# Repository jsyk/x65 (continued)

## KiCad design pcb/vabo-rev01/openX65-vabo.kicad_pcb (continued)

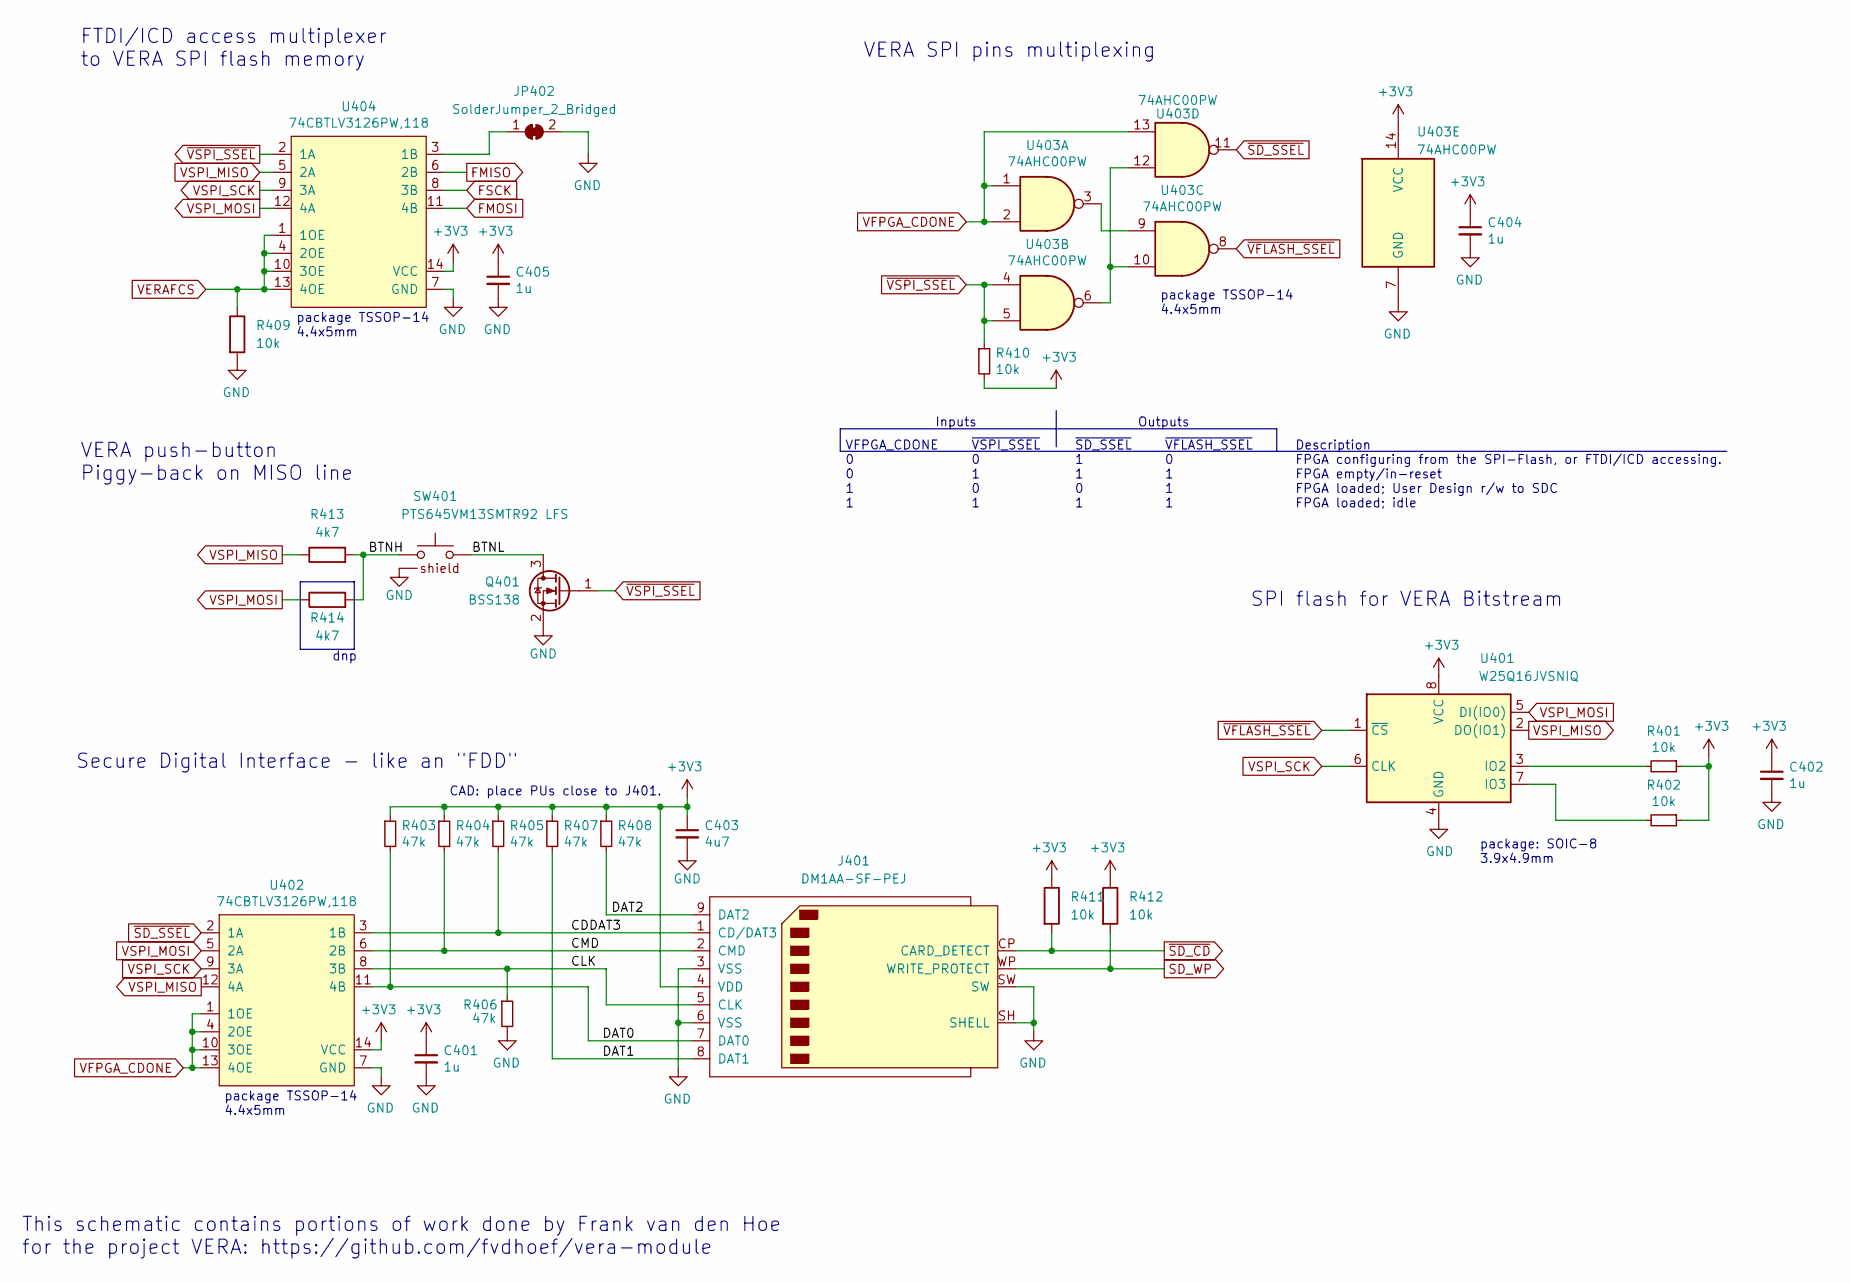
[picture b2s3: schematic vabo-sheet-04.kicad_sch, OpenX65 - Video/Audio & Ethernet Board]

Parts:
C401, C402, C404, C405: 1u; C_0603_1608Metric_Pad1.08x0.95mm_HandSolder
C403: 4u7; C_0603_1608Metric_Pad1.08x0.95mm_HandSolder
J401: DM1AA-SF-PEJ; SD_Hirose_DM1AA_SF_PEJ82
JP402: SolderJumper_2_Bridged; SolderJumper-2_P1.3mm_Bridged_RoundedPad1.0x1.5mm
Q401: BSS138; SOT-23
R401, R402, R409, R410, R411, R412: 10k; R_0603_1608Metric_Pad0.98x0.95mm_HandSolder
R403, R404, R405, R406, R407, R408: 47k; R_0603_1608Metric_Pad0.98x0.95mm_HandSolder
R413, R414: 4k7; R_0603_1608Metric_Pad0.98x0.95mm_HandSolder
SW401: PTS645VM13SMTR92 LFS
U401: W25Q16JVSNIQ; SOIC-8_3.9x4.9mm_P1.27mm
U402, U404: 74CBTLV3126PW,118; TSSOP-14_4.4x5mm_P0.65mm
U403: 74AHC00PW; TSSOP-14_4.4x5mm_P0.65mm

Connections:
+3V3: C401.1, C402.1, C403.1, C404.1, C405.1, J401.4 (VDD), R401.1, R402.1, R403.1, R404.1, R405.1, R407.1, R408.1, R410.2, R411.1, R412.1, U401.8 (VCC), U402.14 (VCC), U403.14 (VCC), U404.14 (VCC); also elsewhere on the board
/VERA SPI-Flash, SDC/BTNH: R413.2, R414.2, SW401.1
/VERA SPI-Flash, SDC/BTNL: Q401.3 (D), SW401.2
/VERA SPI-Flash, SDC/CDDAT3: J401.1 (CD/DAT3), R405.2, U402.3 (1B)
/VERA SPI-Flash, SDC/CLK: J401.5 (CLK), R406.1, U402.8 (3B)
/VERA SPI-Flash, SDC/CMD: J401.2 (CMD), R404.2, U402.6 (2B)
/VERA SPI-Flash, SDC/DAT0: J401.7 (DAT0), R403.2, U402.11 (4B)
/VERA SPI-Flash, SDC/DAT1: J401.8 (DAT1), R407.2
/VERA SPI-Flash, SDC/DAT2: J401.9 (DAT2), R408.2
FMISO: U404.6 (2B); also elsewhere on the board
FMOSI: U404.11 (4B); also elsewhere on the board
FSCK: U404.8 (3B); also elsewhere on the board
GND: C401.2, C402.2, C403.2, C404.2, C405.2, J401.3 (VSS), J401.6 (VSS), J401.SH (SHELL), J401.SW, JP402.2 (B), Q401.2 (S), R406.2, R409.2, SW401.SH, U401.4 (GND), U402.7 (GND), U403.7 (GND), U404.7 (GND); also elsewhere on the board
unnamed: JP402.1 (A), U404.3 (1B)
unnamed: R401.2, U401.3 (IO2)
unnamed: R402.2, U401.7 (IO3)
unnamed: U403.3, U403.9
unnamed: U403.6, U403.10, U403.12
SD_WP: J401.WP (WRITE_PROTECT), R412.2; also elsewhere on the board
VERAFCS: R409.1, U404.1 (1OE), U404.4 (2OE), U404.10 (3OE), U404.13 (4OE); also elsewhere on the board
VFPGA_CDONE: U402.1 (1OE), U402.4 (2OE), U402.10 (3OE), U402.13 (4OE), U403.1, U403.2, U403.13; also elsewhere on the board
VSPI_MISO: R413.1, U401.2 (DO(IO1)), U402.12 (4A), U404.5 (2A); also elsewhere on the board
VSPI_MOSI: R414.1, U401.5 (DI(IO0)), U402.5 (2A), U404.12 (4A); also elsewhere on the board
VSPI_SCK: U401.6 (CLK), U402.9 (3A), U404.9 (3A); also elsewhere on the board
~SD_CD: J401.CP (CARD_DETECT), R411.2; also elsewhere on the board
~SD_SSEL: U402.2 (1A), U403.11
~VFLASH_SSEL: U401.1 (~CS), U403.8
~VSPI_SSEL: Q401.1 (G), R410.1, U403.4, U403.5, U404.2 (1A); also elsewhere on the board

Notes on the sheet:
~{SD_SSEL} 1 1 0 1
This schematic contains portions of work done by Frank van den Hoe for the project VERA: https://github.com/fvdhoef/vera-module
~{VFLASH_SSEL} 0 1 1 1
dnp
Inputs
VFPGA_CDONE 0 0 1 1
package TSSOP-14 4.4x5mm
CAD: place PUs close to J401.
Outputs
package: SOIC-8 3.9x4.9mm
FTDI/ICD access multiplexer to VERA SPI flash memory
Description FPGA configuring from the SPI-Flash, or FTDI/ICD accessing. FPGA empty/in-reset FPGA loaded; User Design r/w to SDC FPGA loaded; idle
~{VSPI_SSEL} 0 1 0 1
Secure Digital Interface - like an "FDD"
SPI flash for VERA Bitstream
VERA push-button Piggy-back on MISO line
VERA SPI pins multiplexing

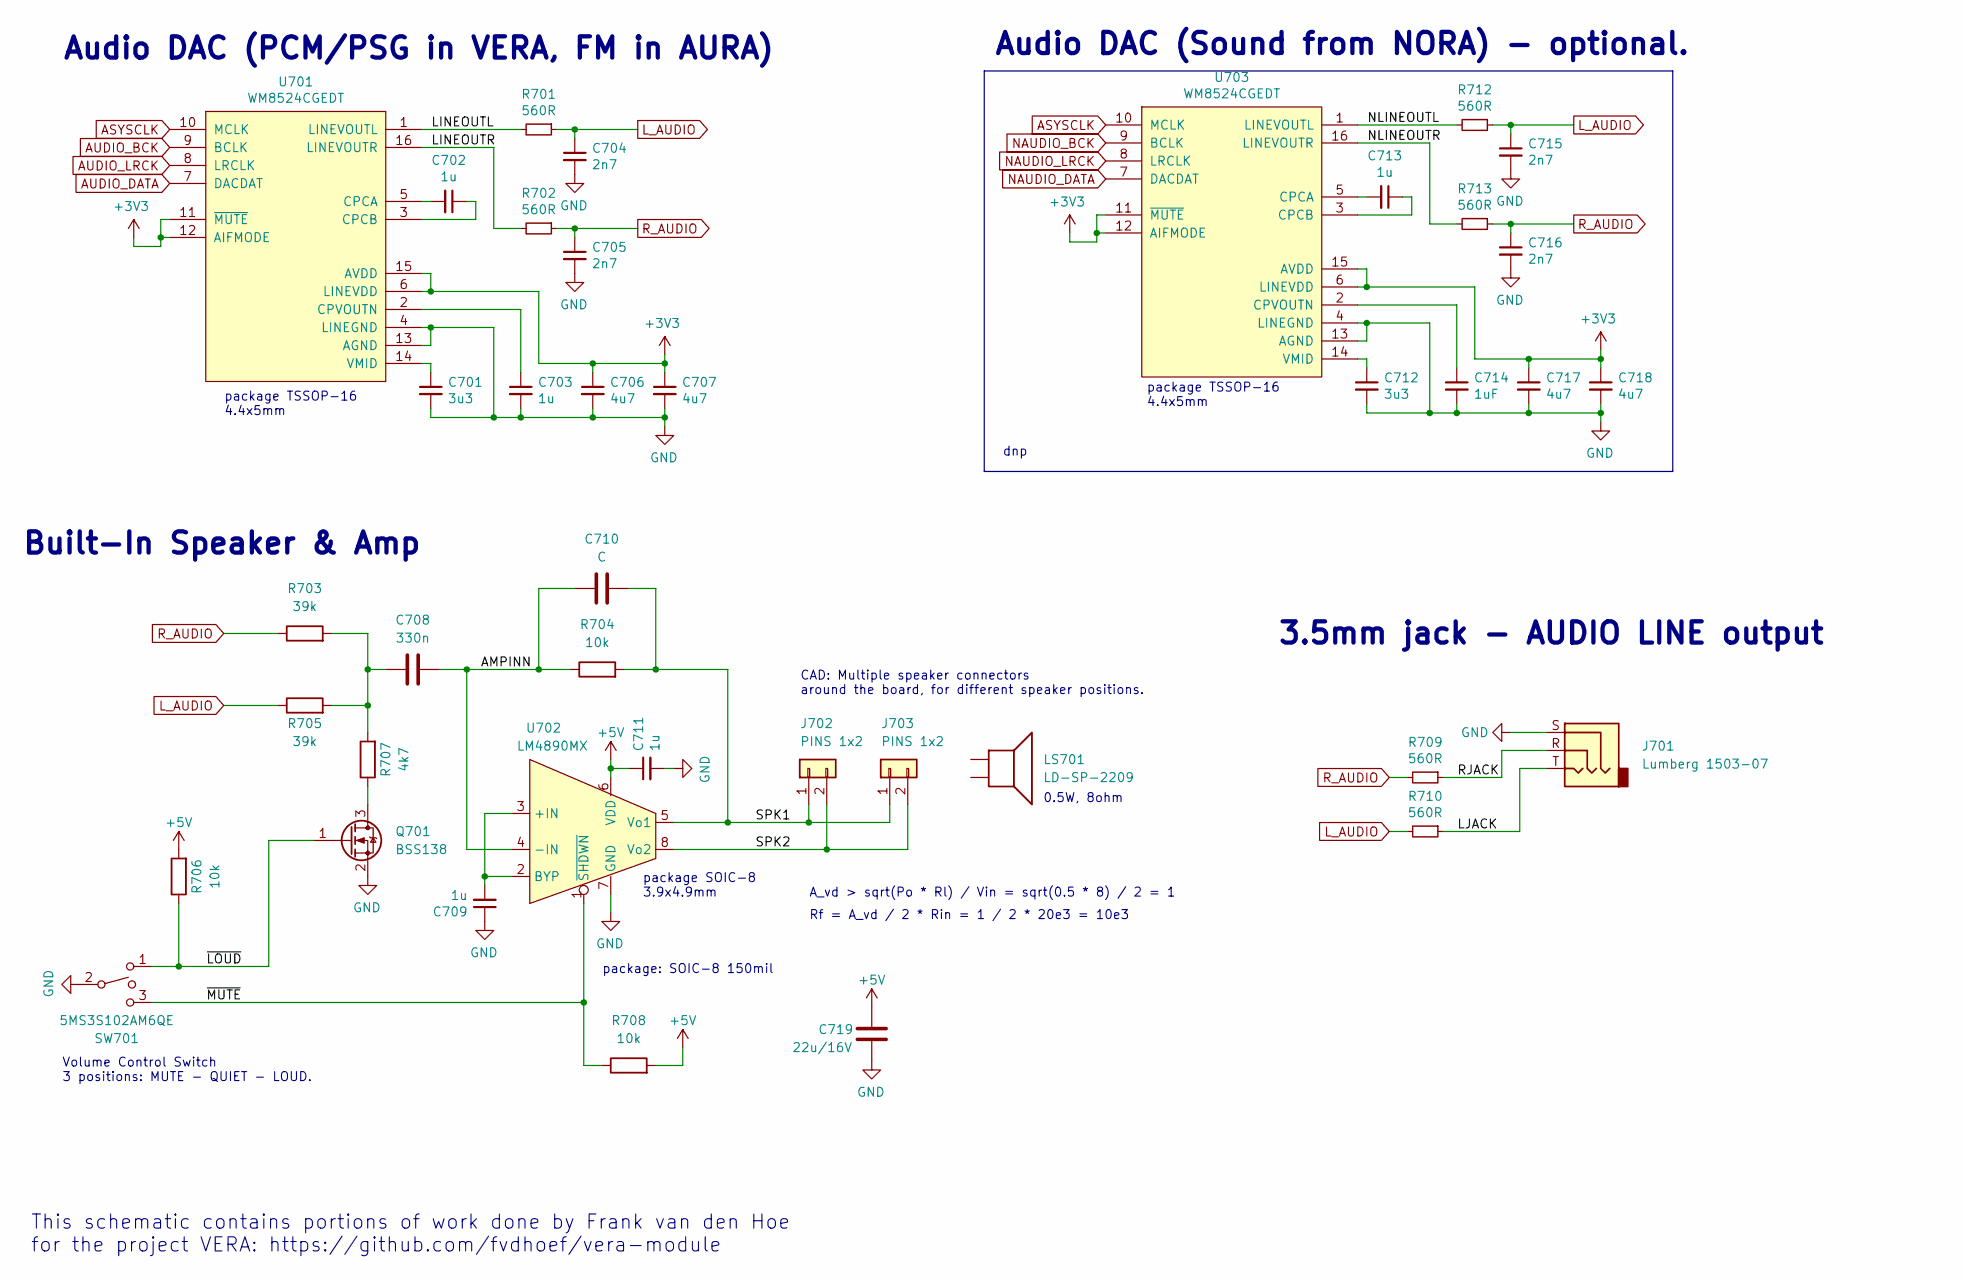
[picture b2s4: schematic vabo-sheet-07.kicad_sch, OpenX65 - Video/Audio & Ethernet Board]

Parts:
C701, C712: 3u3; C_0603_1608Metric_Pad1.08x0.95mm_HandSolder
C702, C703, C709, C711, C713: 1u; C_0603_1608Metric_Pad1.08x0.95mm_HandSolder
C704, C705, C715, C716: 2n7; C_0603_1608Metric_Pad1.08x0.95mm_HandSolder
C706, C707, C717, C718: 4u7; C_0603_1608Metric_Pad1.08x0.95mm_HandSolder
C708: 330n; C_0603_1608Metric_Pad1.08x0.95mm_HandSolder
C710: C; C_0603_1608Metric_Pad1.08x0.95mm_HandSolder
C714: 1uF; C_0603_1608Metric_Pad1.08x0.95mm_HandSolder
C719: 22u/16V; C_0805_2012Metric_Pad1.18x1.45mm_HandSolder
J701: Lumberg 1503-07; Jack_3.5mm_Lumberg_1503_07_Horizontal
J702, J703: PINS 1x2; PinHeader_1x02_P2.54mm_Vertical
LS701: LD-SP-2209
Q701: BSS138; SOT-23
R701, R702, R709, R710, R712, R713: 560R; R_0603_1608Metric_Pad0.98x0.95mm_HandSolder
R703, R705: 39k; R_0603_1608Metric_Pad0.98x0.95mm_HandSolder
R704, R706, R708: 10k; R_0603_1608Metric_Pad0.98x0.95mm_HandSolder
R707: 4k7; R_0603_1608Metric_Pad0.98x0.95mm_HandSolder
SW701: 5MS3S102AM6QE; Switch_5M_M6
U701, U703: WM8524CGEDT; TSSOP-16_4.4x5mm_P0.65mm
U702: LM4890MX; SOIC-8_3.9x4.9mm_P1.27mm

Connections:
+3V3: C706.1, C707.1, C717.1, C718.1, U701.6 (LINEVDD), U701.11 (~MUTE), U701.12 (AIFMODE), U701.15 (AVDD), U703.6 (LINEVDD), U703.11 (~MUTE), U703.12 (AIFMODE), U703.15 (AVDD); also elsewhere on the board
+5V: C711.1, C719.2, R706.2, R708.2, U702.6 (VDD); also elsewhere on the board
/Audio DAC, Output/AMPINN: C708.2, C710.1, R704.1, U702.4 (-IN)
/Audio DAC, Output/LINEOUTL: R701.2, U701.1 (LINEVOUTL)
/Audio DAC, Output/LINEOUTR: R702.2, U701.16 (LINEVOUTR)
/Audio DAC, Output/LJACK: J701.T, R710.1
/Audio DAC, Output/NLINEOUTL: R712.2, U703.1 (LINEVOUTL)
/Audio DAC, Output/NLINEOUTR: R713.2, U703.16 (LINEVOUTR)
/Audio DAC, Output/RJACK: J701.R, R709.1
/Audio DAC, Output/SPK1: C710.2, J702.1, J703.1, R704.2, U702.5 (Vo1)
/Audio DAC, Output/SPK2: J702.2, J703.2, U702.8 (Vo2)
/Audio DAC, Output/~LOUD: Q701.1 (G), R706.1, SW701.1
/Audio DAC, Output/~MUTE: R708.1, SW701.3, U702.1 (~SHDWN)
ASYSCLK: U701.10 (MCLK), U703.10 (MCLK); also elsewhere on the board
AUDIO_BCK: U701.9 (BCLK); also elsewhere on the board
AUDIO_DATA: U701.7 (DACDAT); also elsewhere on the board
AUDIO_LRCK: U701.8 (LRCLK); also elsewhere on the board
GND: C701.2, C703.2, C704.2, C705.2, C706.2, C707.2, C709.1, C711.2, C712.2, C714.2, C715.2, C716.2, C717.2, C718.2, C719.1, J701.S, Q701.2 (S), SW701.2, U701.4 (LINEGND), U701.13 (AGND), U702.7 (GND), U703.4 (LINEGND), U703.13 (AGND); also elsewhere on the board
L_AUDIO: C704.1, C715.1, R701.1, R705.1, R710.2, R712.1
NAUDIO_BCK: U703.9 (BCLK); also elsewhere on the board
NAUDIO_DATA: U703.7 (DACDAT); also elsewhere on the board
NAUDIO_LRCK: U703.8 (LRCLK); also elsewhere on the board
unnamed: C701.1, U701.14 (VMID)
unnamed: C702.1, U701.3 (CPCB)
unnamed: C702.2, U701.5 (CPCA)
unnamed: C703.1, U701.2 (CPVOUTN)
unnamed: C708.1, R703.2, R705.2, R707.2
unnamed: C709.2, U702.2 (BYP), U702.3 (+IN)
unnamed: C712.1, U703.14 (VMID)
unnamed: C713.1, U703.3 (CPCB)
unnamed: C713.2, U703.5 (CPCA)
unnamed: C714.1, U703.2 (CPVOUTN)
unnamed: Q701.3 (D), R707.1
R_AUDIO: C705.1, C716.1, R702.1, R703.1, R709.2, R713.1

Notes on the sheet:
Built-In Speaker & Amp
dnp
package TSSOP-16 4.4x5mm
3.5mm jack - AUDIO LINE output
CAD: Multiple speaker connectors around the board, for different speaker positions.
Audio DAC (Sound from NORA) - optional.
0.5W, 8ohm
A_vd > sqrt(Po * Rl) / Vin = sqrt(0.5 * 8) / 2 = 1
This schematic contains portions of work done by Frank van den Hoe for the project VERA: https://github.com/fvdhoef/vera-module
package: SOIC-8 150mil
Volume Control Switch 3 positions: MUTE - QUIET - LOUD.
Audio DAC (PCM/PSG in VERA, FM in AURA)
package SOIC-8 3.9x4.9mm
Rf = A_vd / 2 * Rin = 1 / 2 * 20e3 = 10e3

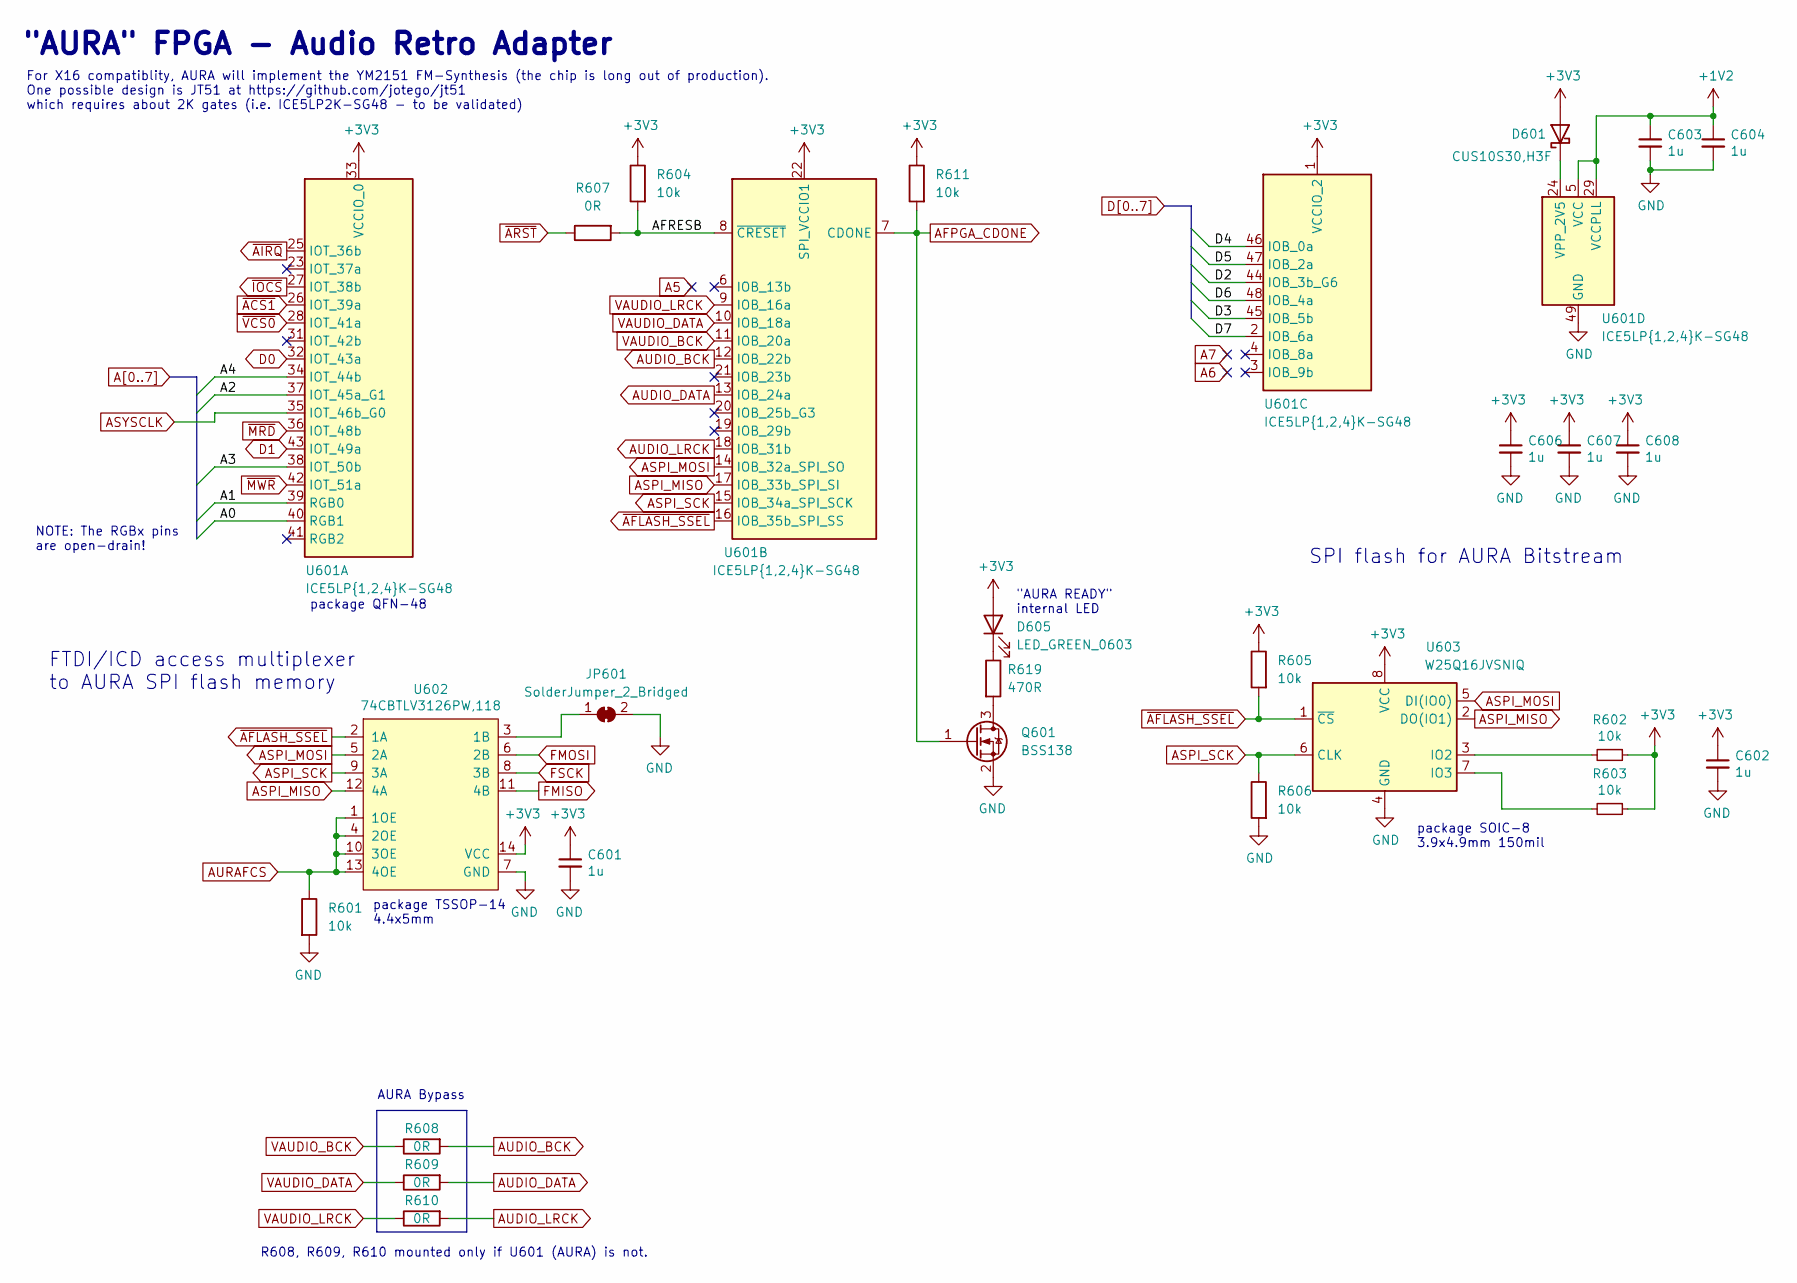
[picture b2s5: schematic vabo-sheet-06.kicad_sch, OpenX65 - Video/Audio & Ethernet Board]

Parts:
C601, C602, C603, C604, C606, C607, C608: 1u; C_0603_1608Metric_Pad1.08x0.95mm_HandSolder
D601: CUS10S30,H3F; D_SOD-323_HandSoldering
D605: LED_GREEN_0603; LED_0603_1608Metric_Pad1.05x0.95mm_HandSolder
JP601: SolderJumper_2_Bridged; SolderJumper-2_P1.3mm_Bridged_RoundedPad1.0x1.5mm
Q601: BSS138; SOT-23
R601, R602, R603, R604, R605, R606, R611: 10k; R_0603_1608Metric_Pad0.98x0.95mm_HandSolder
R607, R608, R609, R610: 0R; R_0603_1608Metric_Pad0.98x0.95mm_HandSolder
R619: 470R; R_0603_1608Metric_Pad0.98x0.95mm_HandSolder
U601: ICE5LP{1,2,4}K-SG48; QFN-48-1EP_7x7mm_P0.5mm_EP5.6x5.6mm
U602: 74CBTLV3126PW,118; TSSOP-14_4.4x5mm_P0.65mm
U603: W25Q16JVSNIQ; SOIC-8_3.9x4.9mm_P1.27mm

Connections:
+1V2: C603.1, C604.1, U601.5 (VCC), U601.29 (VCCPLL), U601.30 (VCC); also elsewhere on the board
+3V3: C601.1, C602.1, C606.1, C607.1, C608.1, D601.2 (A), D605.2 (A), R602.1, R603.1, R604.1, R605.1, R611.1, U601.1 (VCCIO_2), U601.22 (SPI_VCCIO1), U601.33 (VCCIO_0), U602.14 (VCC), U603.8 (VCC); also elsewhere on the board
/Audio AURA FPGA/AFRESB: R604.2, R607.2, U601.8 (~CRESET)
A0: U601.40 (RGB1); also elsewhere on the board
A1: U601.39 (RGB0); also elsewhere on the board
A2: U601.37 (IOT_45a_G1); also elsewhere on the board
A3: U601.38 (IOT_50b); also elsewhere on the board
A4: U601.34 (IOT_44b); also elsewhere on the board
AFPGA_CDONE: Q601.1 (G), R611.2, U601.7 (CDONE); also elsewhere on the board
ASPI_MISO: U601.17 (IOB_33b_SPI_SI), U602.12 (4A), U603.2 (DO(IO1))
ASPI_MOSI: U601.14 (IOB_32a_SPI_SO), U602.5 (2A), U603.5 (DI(IO0))
ASPI_SCK: R606.1, U601.15 (IOB_34a_SPI_SCK), U602.9 (3A), U603.6 (CLK)
ASYSCLK: U601.35 (IOT_46b_G0); also elsewhere on the board
AUDIO_BCK: R608.2, U601.12 (IOB_22b); also elsewhere on the board
AUDIO_DATA: R609.2, U601.13 (IOB_24a); also elsewhere on the board
AUDIO_LRCK: R610.2, U601.18 (IOB_31b); also elsewhere on the board
AURAFCS: R601.1, U602.1 (1OE), U602.4 (2OE), U602.10 (3OE), U602.13 (4OE); also elsewhere on the board
D0: U601.32 (IOT_43a); also elsewhere on the board
D1: U601.43 (IOT_49a); also elsewhere on the board
D2: U601.44 (IOB_3b_G6); also elsewhere on the board
D3: U601.45 (IOB_5b); also elsewhere on the board
D4: U601.46 (IOB_0a); also elsewhere on the board
D5: U601.47 (IOB_2a); also elsewhere on the board
D6: U601.48 (IOB_4a); also elsewhere on the board
D7: U601.2 (IOB_6a); also elsewhere on the board
FMISO: U602.11 (4B); also elsewhere on the board
FMOSI: U602.6 (2B); also elsewhere on the board
FSCK: U602.8 (3B); also elsewhere on the board
GND: C601.2, C602.2, C603.2, C604.2, C606.2, C607.2, C608.2, JP601.2 (B), Q601.2 (S), R601.2, R606.2, U601.49 (GND), U602.7 (GND), U603.4 (GND); also elsewhere on the board
unnamed: D601.1 (K), U601.24 (VPP_2V5)
unnamed: D605.1 (K), R619.1
unnamed: JP601.1 (A), U602.3 (1B)
unnamed: Q601.3 (D), R619.2
unnamed: R602.2, U603.3 (IO2)
unnamed: R603.2, U603.7 (IO3)
VAUDIO_BCK: R608.1, U601.11 (IOB_20a); also elsewhere on the board
VAUDIO_DATA: R609.1, U601.10 (IOB_18a); also elsewhere on the board
VAUDIO_LRCK: R610.1, U601.9 (IOB_16a); also elsewhere on the board
~ACS1: U601.26 (IOT_39a); also elsewhere on the board
~AFLASH_SSEL: R605.2, U601.16 (IOB_35b_SPI_SS), U602.2 (1A), U603.1 (~CS)
~AIRQ: U601.25 (IOT_36b); also elsewhere on the board
~ARST: R607.1; also elsewhere on the board
~IOCS: U601.27 (IOT_38b); also elsewhere on the board
~MRD: U601.36 (IOT_48b); also elsewhere on the board
~MWR: U601.42 (IOT_51a); also elsewhere on the board
~VCS0: U601.28 (IOT_41a); also elsewhere on the board

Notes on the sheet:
R608, R609, R610 mounted only if U601 (AURA) is not.
package TSSOP-14 4.4x5mm
"AURA" FPGA - Audio Retro Adapter
FTDI/ICD access multiplexer to AURA SPI flash memory
SPI flash for AURA Bitstream
package QFN-48
AURA Bypass
NOTE: The RGBx pins are open-drain!
package SOIC-8 3.9x4.9mm 150mil
"AURA READY" internal LED
For X16 compatiblity, AURA will implement the YM2151 FM-Synthesis (the chip is long out of production). One possible design is JT51 at https://github.com/jotego/jt51 which requires about 2K gates (i.e. ICE5LP2K-SG48 - to be validated)

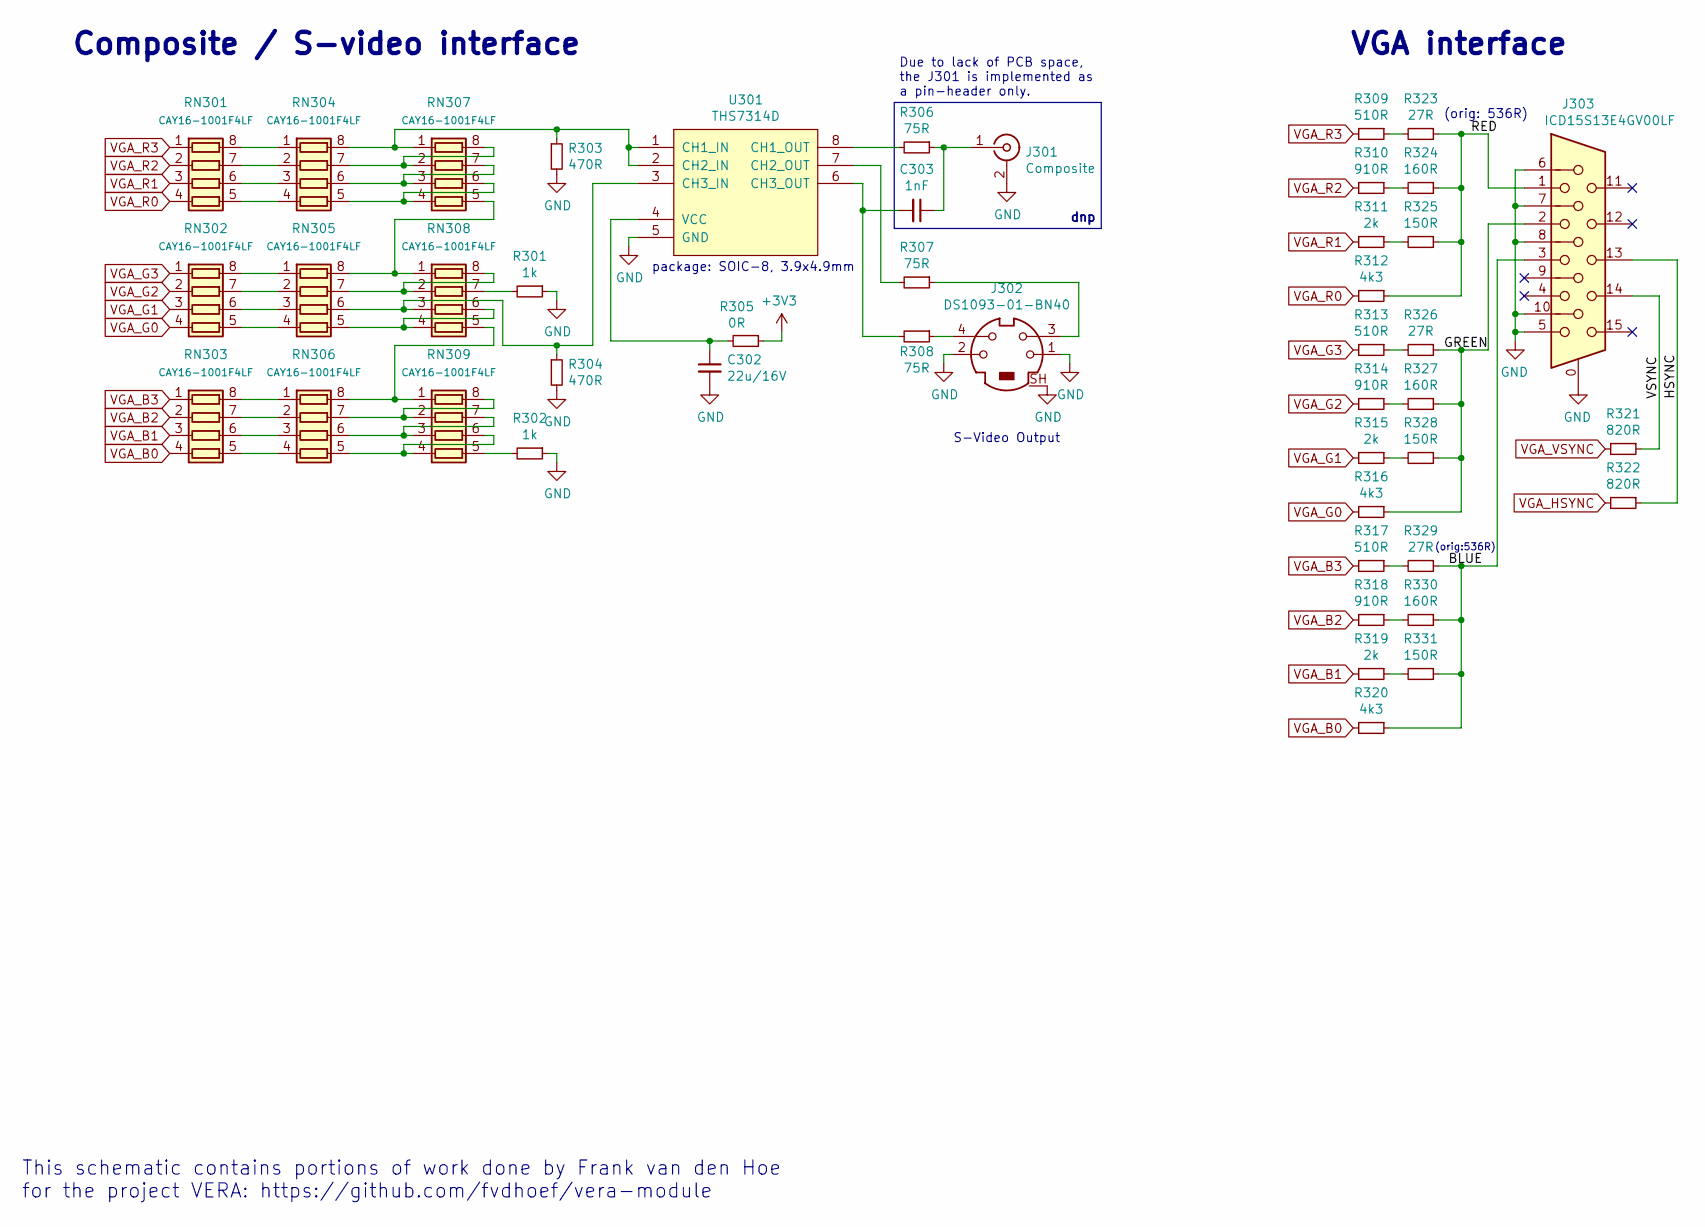
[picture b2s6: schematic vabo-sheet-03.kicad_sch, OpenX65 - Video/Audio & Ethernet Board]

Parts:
C302: 22u/16V; C_0805_2012Metric_Pad1.18x1.45mm_HandSolder
C303: 1nF; C_0603_1608Metric_Pad1.08x0.95mm_HandSolder
J301: Composite; PinHeader_1x02_P2.54mm_Vertical
J302: DS1093-01-BN40
J303: ICD15S13E4GV00LF
R301, R302: 1k; R_0603_1608Metric_Pad0.98x0.95mm_HandSolder
R303, R304: 470R; R_0603_1608Metric_Pad0.98x0.95mm_HandSolder
R305: 0R; R_0603_1608Metric_Pad0.98x0.95mm_HandSolder
R306, R307, R308: 75R; R_0603_1608Metric_Pad0.98x0.95mm_HandSolder
R309, R313, R317: 510R; R_0603_1608Metric_Pad0.98x0.95mm_HandSolder
R310, R314, R318: 910R; R_0603_1608Metric_Pad0.98x0.95mm_HandSolder
R311, R315, R319: 2k; R_0603_1608Metric_Pad0.98x0.95mm_HandSolder
R312, R316, R320: 4k3; R_0603_1608Metric_Pad0.98x0.95mm_HandSolder
R321, R322: 820R; R_0603_1608Metric_Pad0.98x0.95mm_HandSolder
R323, R326, R329: 27R; R_0603_1608Metric_Pad0.98x0.95mm_HandSolder
R324, R327, R330: 160R; R_0603_1608Metric_Pad0.98x0.95mm_HandSolder
R325, R328, R331: 150R; R_0603_1608Metric_Pad0.98x0.95mm_HandSolder
RN301, RN302, RN303, RN304, RN305, RN306, RN307, RN308, RN309: CAY16-1001F4LF; R_Array_Convex_4x0603
U301: THS7314D; SOIC-8_3.9x4.9mm_P1.27mm

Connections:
+3V3: R305.1; also elsewhere on the board
/Video Outputs/BLUE: J303.3, R320.1, R329.1, R330.1, R331.1
/Video Outputs/GREEN: J303.2, R316.1, R326.1, R327.1, R328.1
/Video Outputs/HSYNC: J303.13, R322.1
/Video Outputs/RED: J303.1, R312.1, R323.1, R324.1, R325.1
/Video Outputs/VSYNC: J303.14, R321.1
GND: C302.2, J301.2 (Ext), J302.1, J302.2, J302.SH, J303.0, J303.5, J303.6, J303.7, J303.8, J303.10, R301.1, R302.1, R303.2, R304.2, U301.5 (GND); also elsewhere on the board
unnamed: C302.1, R305.2, U301.4 (VCC)
unnamed: C303.1, J301.1 (In), R306.1
unnamed: C303.2, R308.2, U301.6 (CH3_OUT)
unnamed: J302.3, R307.1
unnamed: J302.4, R308.1
unnamed: R301.2, RN308.7 (R2.2)
unnamed: R302.2, RN309.5 (R4.2)
unnamed: R303.1, RN304.8 (R1.2), RN307.1 (R1.1), U301.1 (CH1_IN), U301.2 (CH2_IN)
unnamed: R304.1, RN305.6 (R3.2), RN308.3 (R3.1), U301.3 (CH3_IN)
unnamed: R306.2, U301.8 (CH1_OUT)
unnamed: R307.2, U301.7 (CH2_OUT)
unnamed: R309.1, R323.2
unnamed: R310.1, R324.2
unnamed: R311.1, R325.2
unnamed: R313.1, R326.2
unnamed: R314.1, R327.2
unnamed: R315.1, R328.2
unnamed: R317.1, R329.2
unnamed: R318.1, R330.2
unnamed: R319.1, R331.2
unnamed: RN301.5 (R4.2), RN304.4 (R4.1)
unnamed: RN301.6 (R3.2), RN304.3 (R3.1)
unnamed: RN301.7 (R2.2), RN304.2 (R2.1)
unnamed: RN301.8 (R1.2), RN304.1 (R1.1)
unnamed: RN302.5 (R4.2), RN305.4 (R4.1)
unnamed: RN302.6 (R3.2), RN305.3 (R3.1)
unnamed: RN302.7 (R2.2), RN305.2 (R2.1)
unnamed: RN302.8 (R1.2), RN305.1 (R1.1)
unnamed: RN303.5 (R4.2), RN306.4 (R4.1)
unnamed: RN303.6 (R3.2), RN306.3 (R3.1)
unnamed: RN303.7 (R2.2), RN306.2 (R2.1)
unnamed: RN303.8 (R1.2), RN306.1 (R1.1)
unnamed: RN304.5 (R4.2), RN307.4 (R4.1), RN307.6 (R3.2)
unnamed: RN304.6 (R3.2), RN307.3 (R3.1), RN307.7 (R2.2)
unnamed: RN304.7 (R2.2), RN307.2 (R2.1), RN307.8 (R1.2)
unnamed: RN305.5 (R4.2), RN308.4 (R4.1), RN308.6 (R3.2)
unnamed: RN305.7 (R2.2), RN308.2 (R2.1), RN308.8 (R1.2)
unnamed: RN305.8 (R1.2), RN307.5 (R4.2), RN308.1 (R1.1)
unnamed: RN306.5 (R4.2), RN309.4 (R4.1), RN309.6 (R3.2)
unnamed: RN306.6 (R3.2), RN309.3 (R3.1), RN309.7 (R2.2)
unnamed: RN306.7 (R2.2), RN309.2 (R2.1), RN309.8 (R1.2)
unnamed: RN306.8 (R1.2), RN308.5 (R4.2), RN309.1 (R1.1)
VGA_B0: R320.2, RN303.4 (R4.1); also elsewhere on the board
VGA_B1: R319.2, RN303.3 (R3.1); also elsewhere on the board
VGA_B2: R318.2, RN303.2 (R2.1); also elsewhere on the board
VGA_B3: R317.2, RN303.1 (R1.1); also elsewhere on the board
VGA_G0: R316.2, RN302.4 (R4.1); also elsewhere on the board
VGA_G1: R315.2, RN302.3 (R3.1); also elsewhere on the board
VGA_G2: R314.2, RN302.2 (R2.1); also elsewhere on the board
VGA_G3: R313.2, RN302.1 (R1.1); also elsewhere on the board
VGA_HSYNC: R322.2; also elsewhere on the board
VGA_R0: R312.2, RN301.4 (R4.1); also elsewhere on the board
VGA_R1: R311.2, RN301.3 (R3.1); also elsewhere on the board
VGA_R2: R310.2, RN301.2 (R2.1); also elsewhere on the board
VGA_R3: R309.2, RN301.1 (R1.1); also elsewhere on the board
VGA_VSYNC: R321.2; also elsewhere on the board

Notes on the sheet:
(orig: 536R)
(orig:536R)
This schematic contains portions of work done by Frank van den Hoe for the project VERA: https://github.com/fvdhoef/vera-module
package: SOIC-8, 3.9x4.9mm
dnp
S-Video Output
VGA interface
Due to lack of PCB space, the J301 is implemented as a pin-header only.
Composite / S-video interface
